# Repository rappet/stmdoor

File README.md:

# STMdoor

A device for interactions of user standing before an locked door.

- Read iButton
- Send iButton code over RS485

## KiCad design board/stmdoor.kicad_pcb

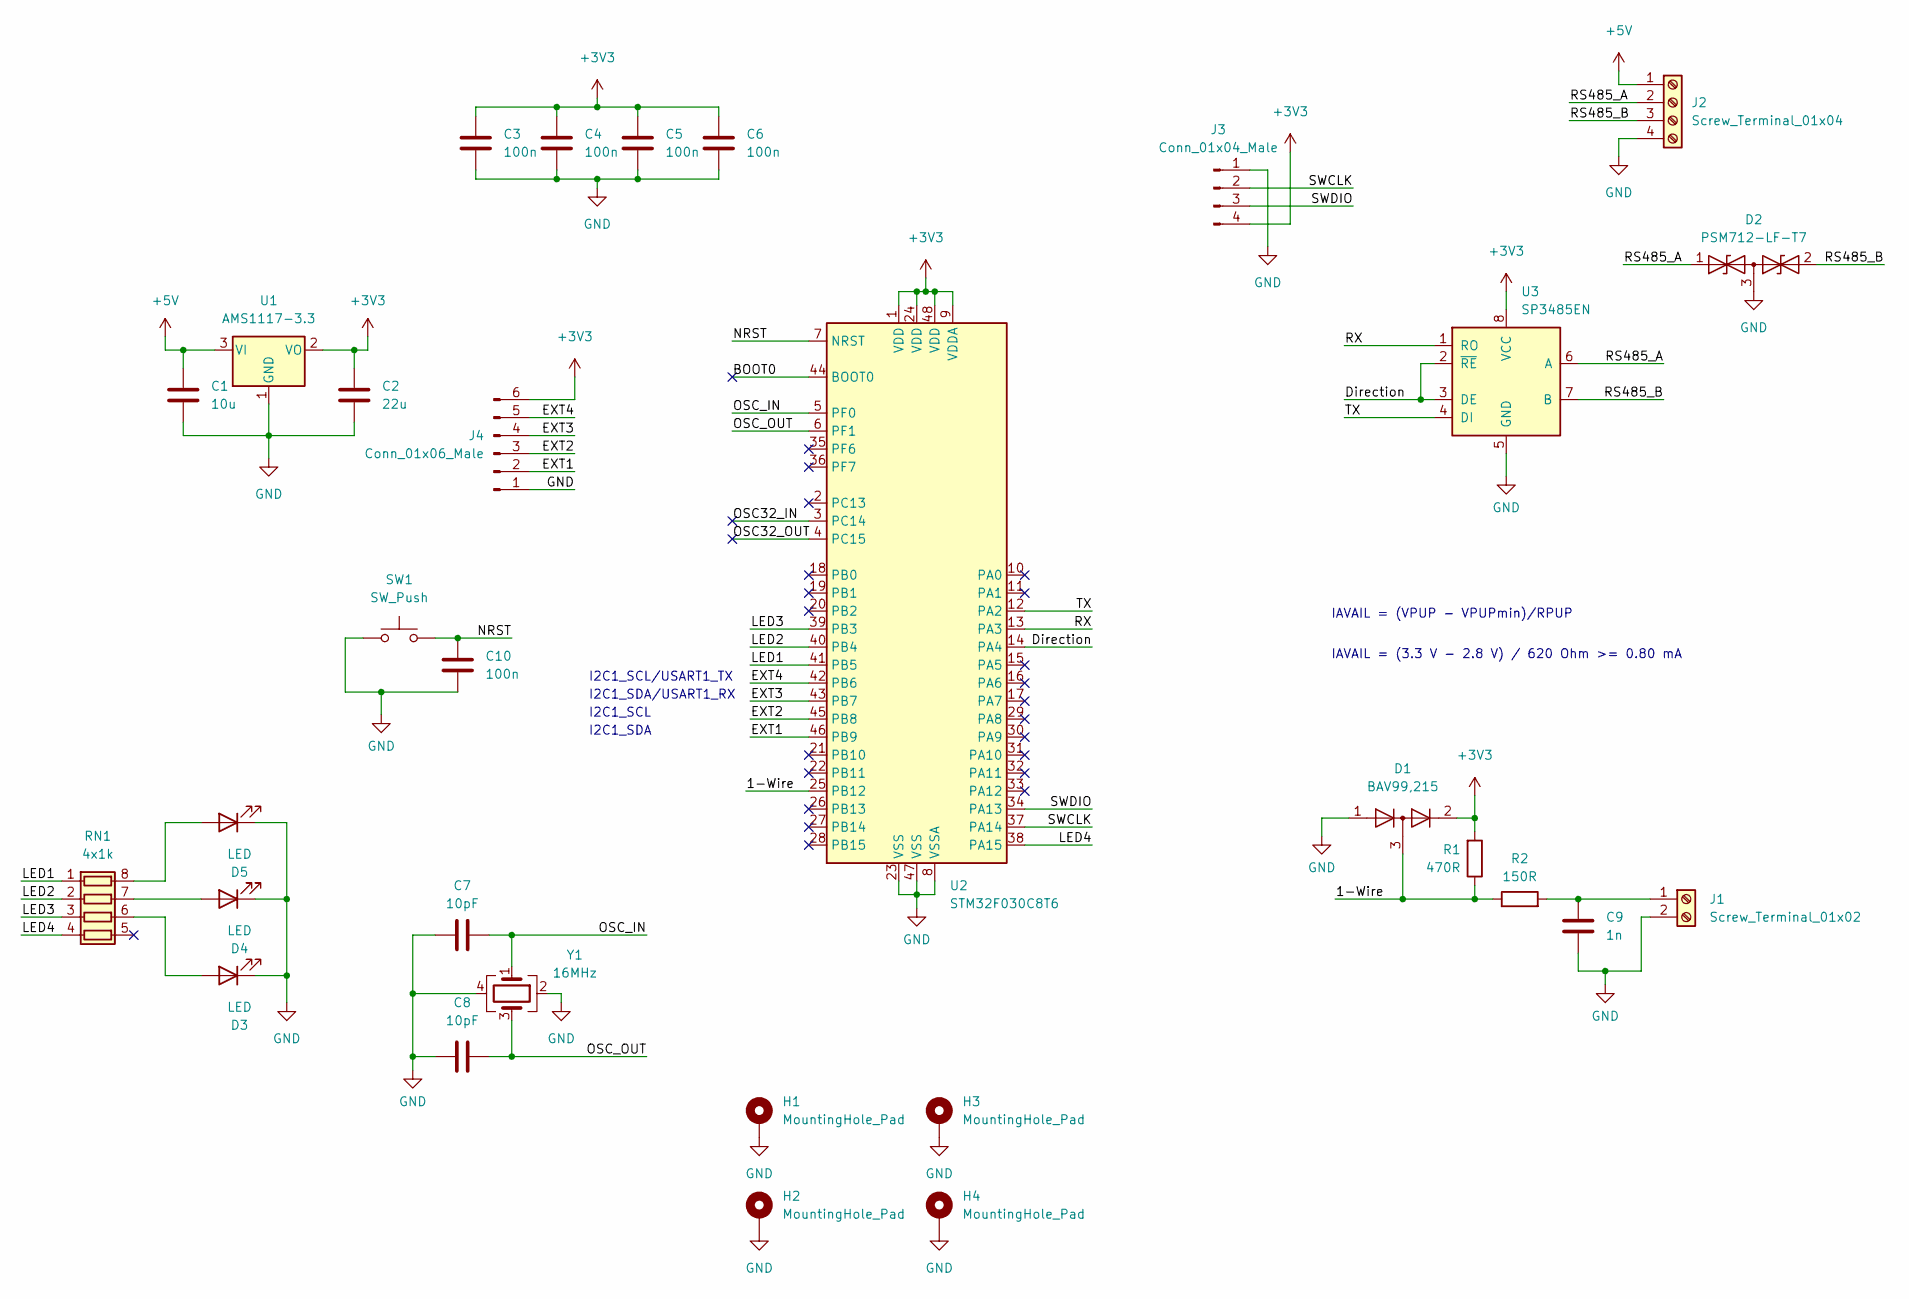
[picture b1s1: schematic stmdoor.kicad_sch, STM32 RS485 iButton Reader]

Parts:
C1: 10u; C_0805_2012Metric; LCSC C440198
C2: 22u; C_0805_2012Metric; LCSC C45783
C3, C4, C5, C6, C10: 100n; C_0402_1005Metric; LCSC C307331
C7, C8: 10pF; C_0402_1005Metric; LCSC C32949
C9: 1n; C_0603_1608Metric; LCSC C1588
D1: BAV99,215; SOT-23; LCSC C2500
D2: PSM712-LF-T7; SOT-23; LCSC C32677
D3, D4, D5: LED; LED_0603_1608Metric; LCSC C2286
H1, H2, H3, H4: MountingHole_Pad; MountingHole_3mm_Pad_Via
J1: Screw_Terminal_01x02; TerminalBlock_Phoenix_MKDS-1,5-2-5.08_1x02_P5.08mm_Horizont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
J2: Screw_Terminal_01x04; TerminalBlock_Phoenix_MKDS-1,5-4-5.08_1x04_P5.08mm_Horizont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
J3: Conn_01x04_Male; PinHeader_1x04_P2.54mm_Horizontal
J4: Conn_01x06_Male; PinHeader_1x06_P2.54mm_Vertical
R1: 470R; R_0805_2012Metric; LCSC C17710
R2: 150R; R_0805_2012Metric; LCSC C17471
RN1: 4x1k; R_Array_Convex_4x0603; LCSC C20197
SW1: SW_Push; SW_Push_1P1T_NO_6x6mm_H9.5mm; LCSC C318884
U1: AMS1117-3.3; SOT-223-3_TabPin2; LCSC C6186
U2: STM32F030C8T6; LQFP-48_7x7mm_P0.5mm; LCSC C23922
U3: SP3485EN; SOIC-8_3.9x4.9mm_P1.27mm; LCSC C8963
Y1: 16MHz; Crystal_SMD_3225-4Pin_3.2x2.5mm; LCSC X322516MLB4SI

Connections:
+3V3: C2.1, C3.1, C4.1, C5.1, C6.1, D1.2 (A), J3.4, J4.6, R1.2, U1.2 (VO), U2.1 (VDD), U2.9 (VDDA), U2.24 (VDD), U2.48 (VDD), U3.8 (VCC)
+5V: C1.1, J2.1, U1.3 (VI)
/1-Wire: D1.3 (K), R1.1, R2.1, U2.25 (PB12)
/BOOT0: U2.44 (BOOT0)
/Direction: U2.14 (PA4), U3.2 (~RE), U3.3 (DE)
/EXT1: J4.2, U2.46 (PB9)
/EXT2: J4.3, U2.45 (PB8)
/EXT3: J4.4, U2.43 (PB7)
/EXT4: J4.5, U2.42 (PB6)
/LED1: RN1.1 (R1.1), U2.41 (PB5)
/LED2: RN1.2 (R2.1), U2.40 (PB4)
/LED3: RN1.3 (R3.1), U2.39 (PB3)
/LED4: RN1.4 (R4.1), U2.38 (PA15)
/NRST: C10.1, SW1.2, U2.7 (NRST)
/OSC32_IN: U2.3 (PC14)
/OSC32_OUT: U2.4 (PC15)
/OSC_IN: C7.2, U2.5 (PF0), Y1.1
/OSC_OUT: C8.2, U2.6 (PF1), Y1.3
/RS485_A: D2.1 (A1), J2.2, U3.6 (A)
/RS485_B: D2.2 (A2), J2.3, U3.7 (B)
/RX: U2.13 (PA3), U3.1 (RO)
/SWCLK: J3.2, U2.37 (PA14)
/SWDIO: J3.3, U2.34 (PA13)
/TX: U2.12 (PA2), U3.4 (DI)
GND: C1.2, C2.2, C3.2, C4.2, C5.2, C6.2, C7.1, C8.1, C9.2, C10.2, D1.1 (K), D2.3 (common), D3.1 (K), D4.1 (K), D5.1 (K), H1.1, H2.1, H3.1, H4.1, J1.2, J2.4, J3.1, J4.1, SW1.1, U1.1 (GND), U2.8 (VSSA), U2.23 (VSS), U2.47 (VSS), U3.5 (GND), Y1.2, Y1.4
unnamed: C9.1, J1.1, R2.2
unnamed: D3.2 (A), RN1.6 (R3.2)
unnamed: D4.2 (A), RN1.7 (R2.2)
unnamed: D5.2 (A), RN1.8 (R1.2)

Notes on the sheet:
I2C1_SCL/USART1_TX
I2C1_SDA/USART1_RX
I2C1_SDA
I2C1_SCL
IAVAIL = (VPUP - VPUPmin)/RPUP
IAVAIL = (3.3 V - 2.8 V) / 620 Ohm >= 0.80 mA

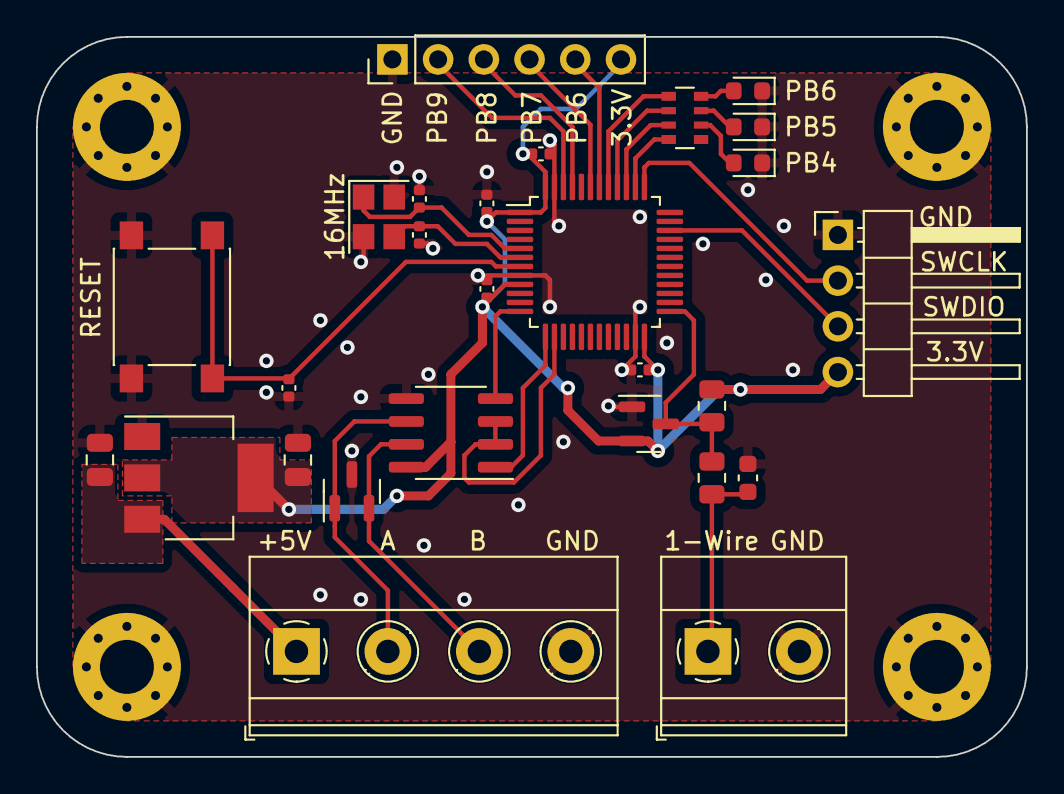
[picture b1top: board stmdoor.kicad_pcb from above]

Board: 2 copper layers, 55.0 x 40.0 mm, 31 parts (0 on the bottom side), 26 nets.

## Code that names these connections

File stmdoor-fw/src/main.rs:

#![no_main]
#![no_std]

extern crate alloc;

use cortex_m_rt::entry;
use embedded_alloc::Heap;
use onewire::{DeviceSearch, OneWire};
use panic_halt as _;
use stm32f0xx_hal as hal;

use alloc::format;
use core::fmt::Write;

use crate::hal::{delay::Delay, pac, prelude::*, serial::Serial};

#[global_allocator]
static HEAP: Heap = Heap::empty();

#[entry]
fn main() -> ! {
    {
        use core::mem::MaybeUninit;
        const HEAP_SIZE: usize = 1024;
        static mut HEAP_MEM: [MaybeUninit<u8>; HEAP_SIZE] = [MaybeUninit::uninit(); HEAP_SIZE];
        unsafe { HEAP.init(HEAP_MEM.as_ptr() as usize, HEAP_SIZE) }
    }

    let mut p = pac::Peripherals::take().unwrap();
    let cp = cortex_m::peripheral::Peripherals::take().unwrap();

    let mut rcc = p.RCC.configure().sysclk(16.mhz()).freeze(&mut p.FLASH);

    let gpioa = p.GPIOA.split(&mut rcc);
    let gpiob = p.GPIOB.split(&mut rcc);

    // changed after Rev. 1.2
    let mut led1 = cortex_m::interrupt::free(|cs| gpiob.pb6.into_push_pull_output(cs));
    let mut led2 = cortex_m::interrupt::free(|cs| gpiob.pb5.into_push_pull_output(cs));
    let mut led3 = cortex_m::interrupt::free(|cs| gpiob.pb4.into_push_pull_output(cs));

    /*
    // available since Rev. 1.2
    let mut _ext1 = cortex_m::interrupt::free(|cs| gpiob.pb9.into_push_pull_output(cs));
    let mut _ext2 = cortex_m::interrupt::free(|cs| gpiob.pb8.into_push_pull_output(cs));
    let mut _ext3 = cortex_m::interrupt::free(|cs| gpiob.pb7.into_push_pull_output(cs));
    let mut _ext4 = cortex_m::interrupt::free(|cs| gpiob.pb6.into_push_pull_output(cs));
    */

    let mut dir = cortex_m::interrupt::free(|cs| gpioa.pa4.into_push_pull_output(cs));
    dir.set_high().ok();

    let (tx, rx) = cortex_m::interrupt::free(move |cs| {
        (
            gpioa.pa2.into_alternate_af1(cs),
            gpioa.pa3.into_alternate_af1(cs),
        )
    });
    let mut serial = Serial::usart2(p.USART2, (tx, rx), 9600.bps(), &mut rcc);

    let mut delay = Delay::new(cp.SYST, &rcc);

    let mut one_wire_pin = cortex_m::interrupt::free(|cs| gpiob.pb12.into_open_drain_output(cs));
    let mut one_wire = OneWire::new(&mut one_wire_pin, false);

    if one_wire.reset(&mut delay).is_err() {
        loop {}
    }

    led1.set_high().ok();

    loop {
        led2.set_high().ok();
        let mut search = DeviceSearch::new();
        while let Some(device) = one_wire.search_next(&mut search, &mut delay).unwrap() {
            led3.set_high().ok();
            let address = &device.address;

            let formatted = format!("one-wire-addr {address:?}\n");
            serial.write_str(&formatted).ok();

            delay.delay_ms(100_u16);
            led3.set_low().ok();
        }
        led2.set_low().ok();

        delay.delay_ms(100_u16);
    }
}

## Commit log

2023-06-05 Initial Commit - Rev 1
2023-06-05 Replace switch with SMD switch
2023-06-06 Added missing connection to MCU for 1-Wire bus
2023-06-06 Add label to crystal
2023-06-06 Change LEDs and add future upgrade header
2023-06-06 Move hardware to board folder
2023-06-06 Add firmware
